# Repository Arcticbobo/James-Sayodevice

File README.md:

# James-Sayodevice
Repository containing files for a custom sayodevice
I created this macropad to allow me to play osu! on the go, and become more efficient when Designing mechanisms for my vex V5 team.

Overall design:

Schematic for circuit:

PCB:

Case Design:

BOM:
 - 4x Cherry MX keyboard switch
 - 1x XIAO RP2040 
 - 2x SK6812MINI-E LED
 - 4x Blank DSA keycaps
 - 4x M3x16mm screws
 - 4x M3x5mx4mm heatset inserts
 - 1x 0.91 inch OLED display

Custom:
 - case lid.stl
 - case base.stl
 - KMK Firmware (I will finish adding code for display once I have hardware for troubleshooting purposes)

Final Product

After some struggles, tweaking, tinkering, and testing, here is the final product!

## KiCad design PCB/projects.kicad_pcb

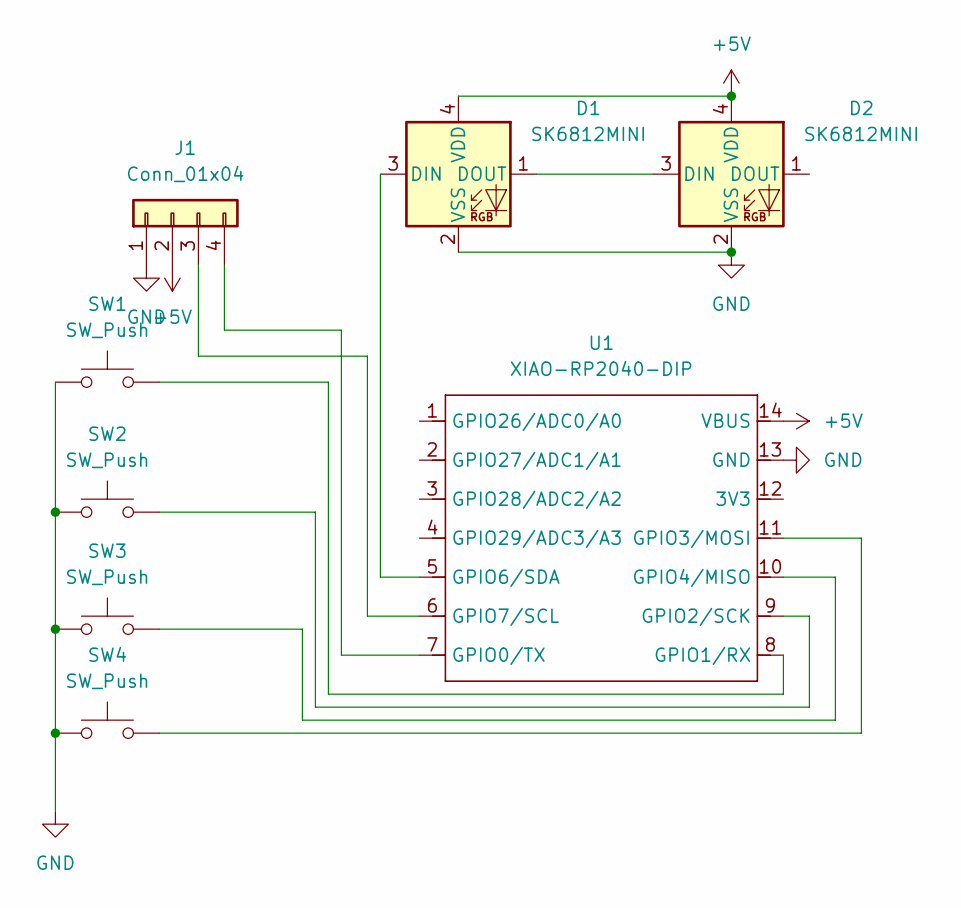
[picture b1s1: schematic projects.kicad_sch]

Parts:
D1, D2: SK6812MINI; LED_SK6812MINI_PLCC4_3.5x3.5mm_P1.75mm
J1: Conn_01x04; SSD1306-0.91-OLED-4pin-128x32
SW1, SW2, SW3, SW4: SW_Push; SW_Cherry_MX_1.00u_PCB
U1: XIAO-RP2040-DIP

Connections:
+5V: D1.4 (VDD), D2.4 (VDD), J1.2, U1.14 (VBUS)
GND: D1.2 (VSS), D2.2 (VSS), J1.1, SW1.1, SW2.1, SW3.1, SW4.1, U1.13 (GND)
unnamed: D1.3 (DIN), U1.5 (GPIO6/SDA)
unnamed: D1.1 (DOUT), D2.3 (DIN)
unnamed: J1.3, U1.6 (GPIO7/SCL)
unnamed: J1.4, U1.7 (GPIO0/TX)
unnamed: SW1.2, U1.8 (GPIO1/RX)
unnamed: SW2.2, U1.9 (GPIO2/SCK)
unnamed: SW4.2, U1.11 (GPIO3/MOSI)
unnamed: SW3.2, U1.10 (GPIO4/MISO)

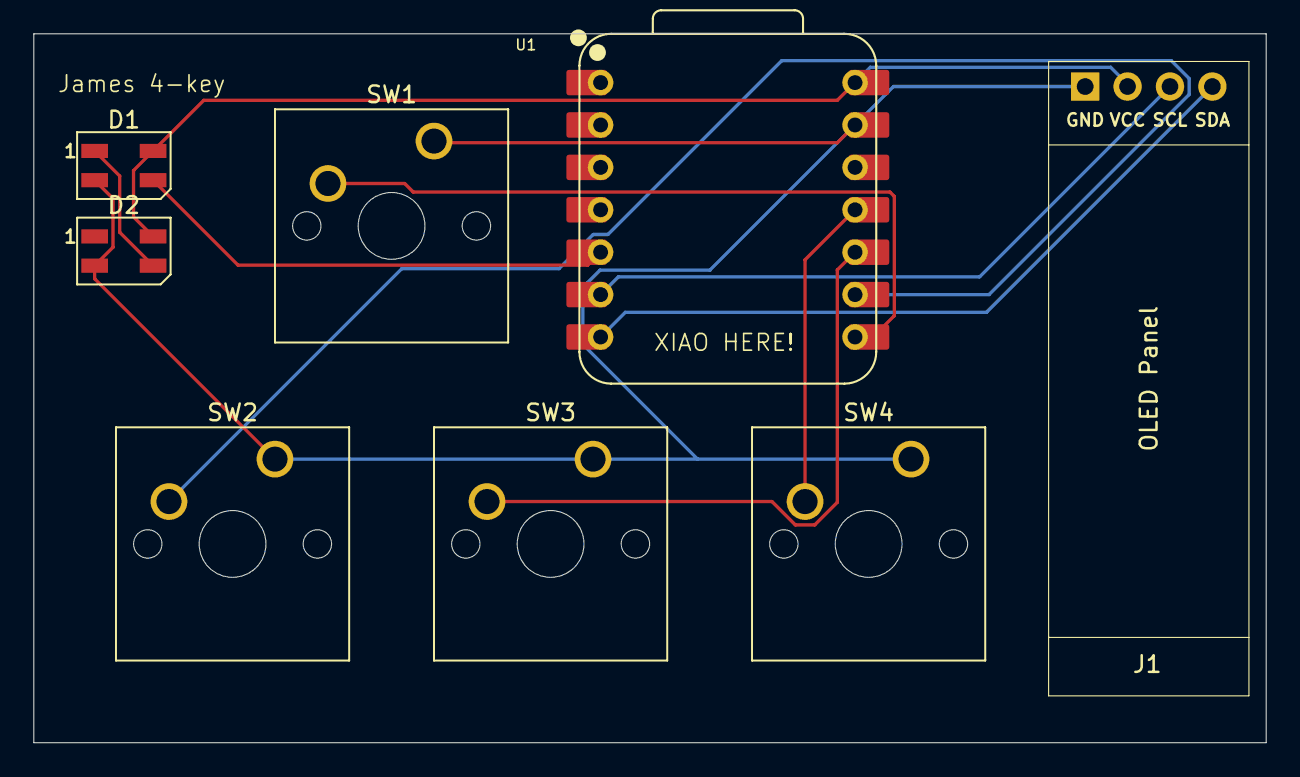
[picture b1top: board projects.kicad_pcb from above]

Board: 2 copper layers, 73.8 x 42.5 mm, 8 parts (0 on the bottom side), 10 nets.

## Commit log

2026-02-03 Update README with final product details
    Added final product image and description to README.
